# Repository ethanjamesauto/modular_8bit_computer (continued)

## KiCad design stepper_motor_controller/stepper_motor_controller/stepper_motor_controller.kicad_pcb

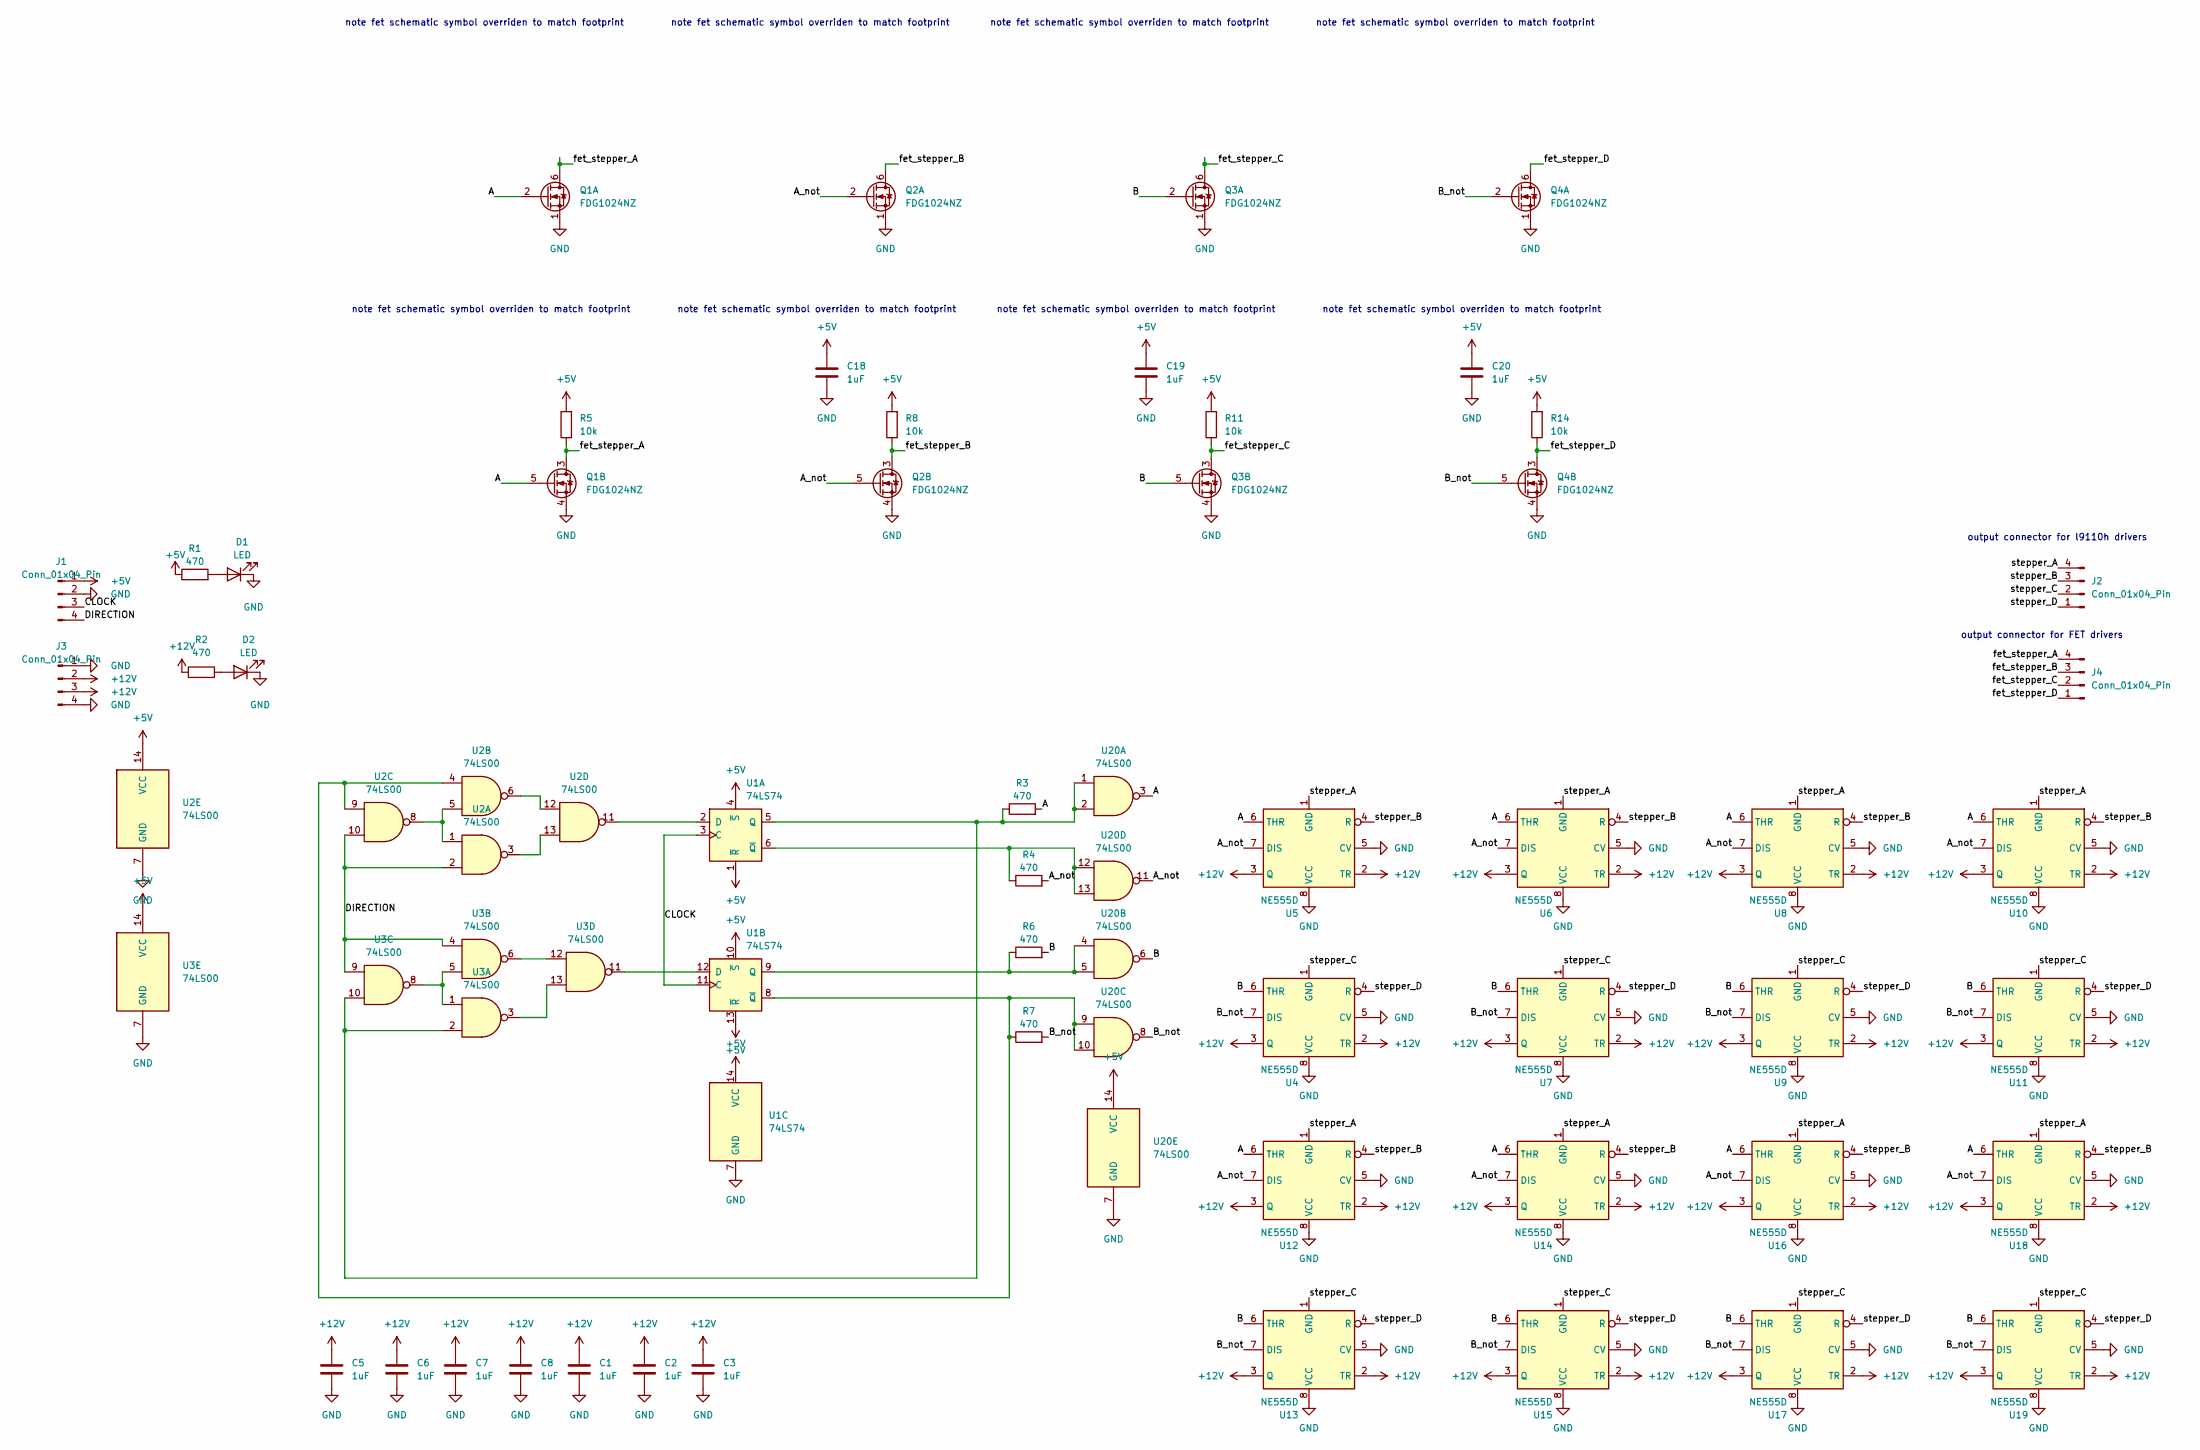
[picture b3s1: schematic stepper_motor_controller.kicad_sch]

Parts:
C1, C2, C3, C5, C6, C7, C8, C18, C19, C20: 1uF; C_0603_1608Metric
D1, D2: LED; R_0603_1608Metric
J1, J2, J3, J4: Conn_01x04_Pin; PinHeader_1x04_P2.54mm_Vertical
Q1, Q2, Q3, Q4: FDG1024NZ; SOT-23-6_Handsoldering
R1, R2, R3, R4, R6, R7: 470; R_0603_1608Metric
R5, R8, R11, R14: 10k; R_Axial_DIN0204_L3.6mm_D1.6mm_P5.08mm_Horizontal
U1: 74LS74; DIP-14_W7.62mm
U2, U3, U20: 74LS00; DIP-14_W7.62mm
U4, U5, U6, U7, U8, U9, U10, U11, U12, U13, U14, U15, U16, U17, U18, U19: NE555D; DIP-8_W7.62mm

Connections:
+5V: C18.1, C19.1, C20.1, J1.1, R1.1, R5.2, R8.2, R11.2, R14.2, U1.1 (~R), U1.4 (~S), U1.10 (~S), U1.13 (~R), U1.14 (VCC), U2.14 (VCC), U3.14 (VCC), U20.14 (VCC)
+12V: C1.1, C2.1, C3.1, C5.1, C6.1, C7.1, C8.1, J3.2, J3.3, R2.1, U4.2 (TR), U4.3 (Q), U5.2 (TR), U5.3 (Q), U6.2 (TR), U6.3 (Q), U7.2 (TR), U7.3 (Q), U8.2 (TR), U8.3 (Q), U9.2 (TR), U9.3 (Q), U10.2 (TR), U10.3 (Q), U11.2 (TR), U11.3 (Q), U12.2 (TR), U12.3 (Q), U13.2 (TR), U13.3 (Q), U14.2 (TR), U14.3 (Q), U15.2 (TR), U15.3 (Q), U16.2 (TR), U16.3 (Q), U17.2 (TR), U17.3 (Q), U18.2 (TR), U18.3 (Q), U19.2 (TR), U19.3 (Q)
/A: Q1.2 (G), Q1.5 (G), R3.2, U5.6 (THR), U6.6 (THR), U8.6 (THR), U10.6 (THR), U12.6 (THR), U14.6 (THR), U16.6 (THR), U18.6 (THR), U20.3
/A_not: Q2.2 (G), Q2.5 (G), R4.2, U5.7 (DIS), U6.7 (DIS), U8.7 (DIS), U10.7 (DIS), U12.7 (DIS), U14.7 (DIS), U16.7 (DIS), U18.7 (DIS), U20.11
/B: Q3.2 (G), Q3.5 (G), R6.2, U4.6 (THR), U7.6 (THR), U9.6 (THR), U11.6 (THR), U13.6 (THR), U15.6 (THR), U17.6 (THR), U19.6 (THR), U20.6
/B_not: Q4.2 (G), Q4.5 (G), R7.2, U4.7 (DIS), U7.7 (DIS), U9.7 (DIS), U11.7 (DIS), U13.7 (DIS), U15.7 (DIS), U17.7 (DIS), U19.7 (DIS), U20.8
/CLOCK: J1.3, U1.3 (C), U1.11 (C)
/DIRECTION: J1.4, U2.2, U2.10, U3.4, U3.9
/fet_stepper_A: J4.4, Q1.3 (D), Q1.6 (D), R5.1
/fet_stepper_B: J4.3, Q2.3 (D), Q2.6 (D), R8.1
/fet_stepper_C: J4.2, Q3.3 (D), Q3.6 (D), R11.1
/fet_stepper_D: J4.1, Q4.3 (D), Q4.6 (D), R14.1
/stepper_A: J2.4, U5.1 (GND), U6.1 (GND), U8.1 (GND), U10.1 (GND), U12.1 (GND), U14.1 (GND), U16.1 (GND), U18.1 (GND)
/stepper_B: J2.3, U5.4 (R), U6.4 (R), U8.4 (R), U10.4 (R), U12.4 (R), U14.4 (R), U16.4 (R), U18.4 (R)
/stepper_C: J2.2, U4.1 (GND), U7.1 (GND), U9.1 (GND), U11.1 (GND), U13.1 (GND), U15.1 (GND), U17.1 (GND), U19.1 (GND)
/stepper_D: J2.1, U4.4 (R), U7.4 (R), U9.4 (R), U11.4 (R), U13.4 (R), U15.4 (R), U17.4 (R), U19.4 (R)
GND: C1.2, C2.2, C3.2, C5.2, C6.2, C7.2, C8.2, C18.2, C19.2, C20.2, D1.1 (K), D2.1 (K), J1.2, J3.1, J3.4, Q1.1 (S), Q1.4 (S), Q2.1 (S), Q2.4 (S), Q3.1 (S), Q3.4 (S), Q4.1 (S), Q4.4 (S), U1.7 (GND), U2.7 (GND), U3.7 (GND), U4.5 (CV), U4.8 (VCC), U5.5 (CV), U5.8 (VCC), U6.5 (CV), U6.8 (VCC), U7.5 (CV), U7.8 (VCC), U8.5 (CV), U8.8 (VCC), U9.5 (CV), U9.8 (VCC), U10.5 (CV), U10.8 (VCC), U11.5 (CV), U11.8 (VCC), U12.5 (CV), U12.8 (VCC), U13.5 (CV), U13.8 (VCC), U14.5 (CV), U14.8 (VCC), U15.5 (CV), U15.8 (VCC), U16.5 (CV), U16.8 (VCC), U17.5 (CV), U17.8 (VCC), U18.5 (CV), U18.8 (VCC), U19.5 (CV), U19.8 (VCC), U20.7 (GND)
unnamed: D1.2 (A), R1.2
unnamed: D2.2 (A), R2.2
unnamed: U1.2 (D), U2.11
unnamed: R3.1, U1.5 (Q), U3.2, U3.10, U20.1, U20.2
unnamed: R4.1, U1.6 (~Q), U20.12, U20.13
unnamed: U1.12 (D), U3.11
unnamed: R6.1, U1.9 (Q), U20.4, U20.5
unnamed: R7.1, U1.8 (~Q), U2.4, U2.9, U20.9, U20.10
unnamed: U2.1, U2.5, U2.8
unnamed: U2.6, U2.12
unnamed: U2.3, U2.13
unnamed: U3.1, U3.5, U3.8
unnamed: U3.6, U3.12
unnamed: U3.3, U3.13

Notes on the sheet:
note fet schematic symbol overriden to match footprint
output connector for l9110h drivers
output connector for FET drivers

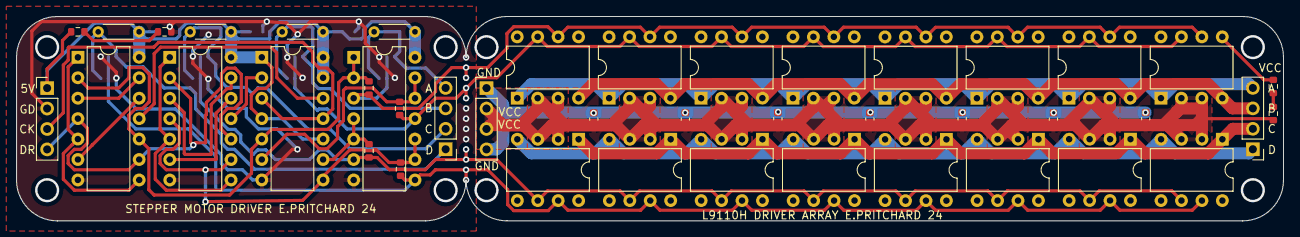
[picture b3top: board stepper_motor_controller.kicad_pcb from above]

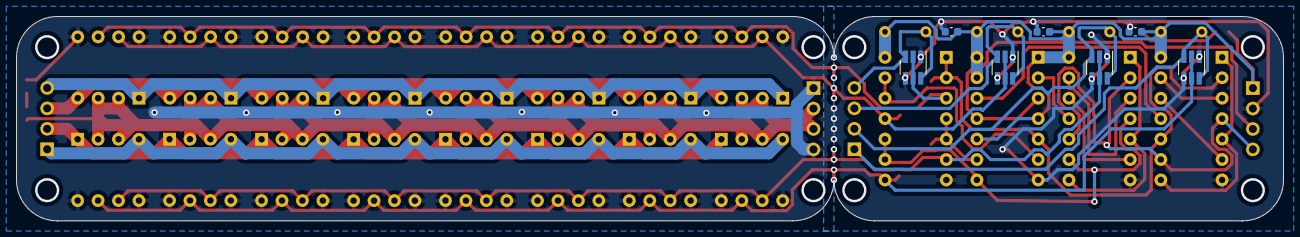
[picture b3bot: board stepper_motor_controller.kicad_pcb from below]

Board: 2 copper layers, 157.5 x 25.4 mm, 50 parts (7 on the bottom side), 31 nets.

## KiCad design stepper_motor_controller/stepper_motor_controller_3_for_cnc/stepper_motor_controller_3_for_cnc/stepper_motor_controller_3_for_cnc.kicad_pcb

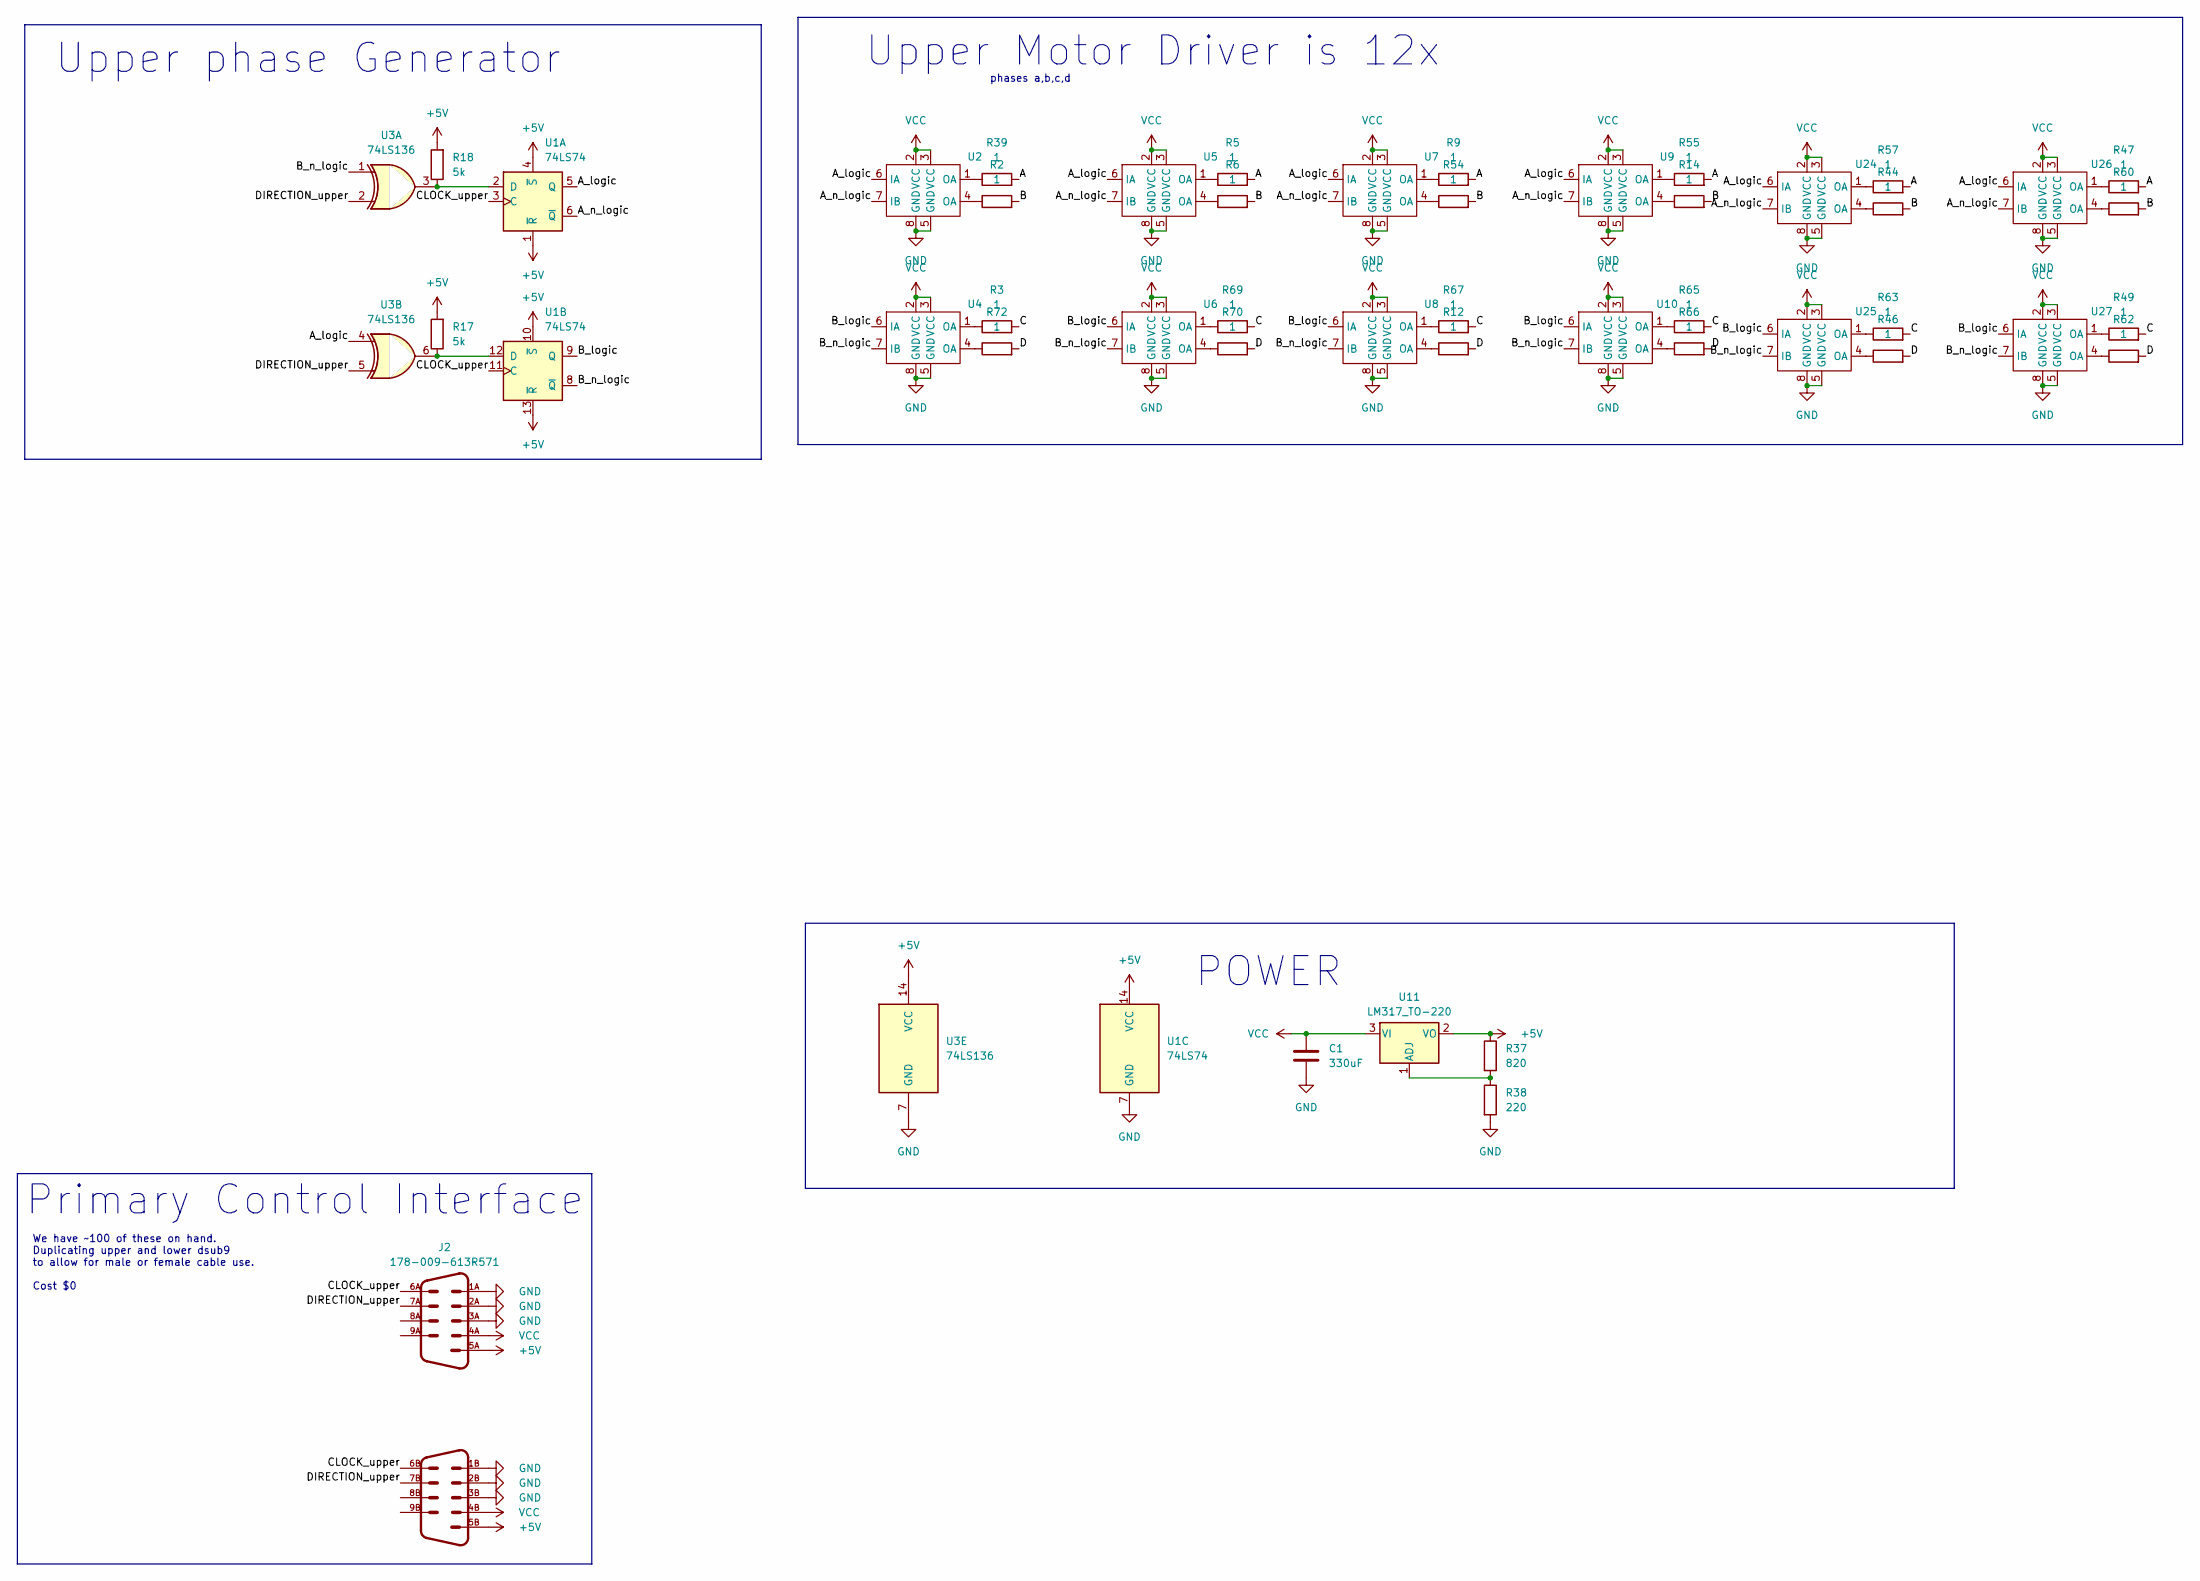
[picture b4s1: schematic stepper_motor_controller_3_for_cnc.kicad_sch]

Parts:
C1: 330uF
J2: 178-009-613R571
R2, R3, R5, R6, R9, R12, R14, R39, R44, R46, R47, R49, R54, R55, R57, R60, R62, R63, R65, R66, R67, R69, R70, R72: 1; R_1206_3216Metric
R17, R18: 5k; R_Axial_DIN0204_L3.6mm_D1.6mm_P5.08mm_Horizontal
R37: 820; R_Axial_DIN0204_L3.6mm_D1.6mm_P5.08mm_Horizontal
R38: 220; R_Axial_DIN0204_L3.6mm_D1.6mm_P5.08mm_Horizontal
U1: 74LS74; DIP-14_W7.62mm
U2, U4, U5, U6, U7, U8, U9, U10, U24, U25, U26, U27: DIP-8_W7.62mm
U3: 74LS136; DIP-14_W7.62mm
U11: LM317_TO-220; TO-220-3_Vertical

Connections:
+5V: J2.5A, J2.5B, R17.2, R18.2, R37.1, U1.1 (~R), U1.4 (~S), U1.10 (~S), U1.13 (~R), U1.14 (VCC), U3.14 (VCC), U11.2 (VO)
/A: R5.2, R9.2, R39.2, R47.2, R55.2, R57.2
/A_logic: U1.5 (Q), U2.6 (IA), U3.4, U5.6 (IA), U7.6 (IA), U9.6 (IA), U24.6 (IA), U26.6 (IA)
/A_n_logic: U1.6 (~Q), U2.7 (IB), U5.7 (IB), U7.7 (IB), U9.7 (IB), U24.7 (IB), U26.7 (IB)
/B: R2.2, R6.2, R14.2, R44.2, R54.2, R60.2
/B_logic: U1.9 (Q), U4.6 (IA), U6.6 (IA), U8.6 (IA), U10.6 (IA), U25.6 (IA), U27.6 (IA)
/B_n_logic: U1.8 (~Q), U3.1, U4.7 (IB), U6.7 (IB), U8.7 (IB), U10.7 (IB), U25.7 (IB), U27.7 (IB)
/C: R3.2, R49.2, R63.2, R65.2, R67.2, R69.2
/CLOCK_upper: J2.6A, J2.6B, U1.3 (C), U1.11 (C)
/D: R12.2, R46.2, R62.2, R66.2, R70.2, R72.2
/DIRECTION_upper: J2.7A, J2.7B, U3.2, U3.5
GND: C1.2, J2.1A, J2.1B, J2.2A, J2.2B, J2.3A, J2.3B, R38.2, U1.7 (GND), U2.5 (GND), U2.8 (GND), U3.7 (GND), U4.5 (GND), U4.8 (GND), U5.5 (GND), U5.8 (GND), U6.5 (GND), U6.8 (GND), U7.5 (GND), U7.8 (GND), U8.5 (GND), U8.8 (GND), U9.5 (GND), U9.8 (GND), U10.5 (GND), U10.8 (GND), U24.5 (GND), U24.8 (GND), U25.5 (GND), U25.8 (GND), U26.5 (GND), U26.8 (GND), U27.5 (GND), U27.8 (GND)
unnamed: R2.1, U2.4 (OA)
unnamed: R3.1, U4.1 (OA)
unnamed: R5.1, U5.1 (OA)
unnamed: R6.1, U5.4 (OA)
unnamed: R9.1, U7.1 (OA)
unnamed: R12.1, U8.4 (OA)
unnamed: R14.1, U9.4 (OA)
unnamed: R39.1, U2.1 (OA)
unnamed: R44.1, U24.4 (OA)
unnamed: R46.1, U25.4 (OA)
unnamed: R47.1, U26.1 (OA)
unnamed: R49.1, U27.1 (OA)
unnamed: R54.1, U7.4 (OA)
unnamed: R55.1, U9.1 (OA)
unnamed: R57.1, U24.1 (OA)
unnamed: R60.1, U26.4 (OA)
unnamed: R62.1, U27.4 (OA)
unnamed: R63.1, U25.1 (OA)
unnamed: R65.1, U10.1 (OA)
unnamed: R66.1, U10.4 (OA)
unnamed: R67.1, U8.1 (OA)
unnamed: R69.1, U6.1 (OA)
unnamed: R70.1, U6.4 (OA)
unnamed: R72.1, U4.4 (OA)
unnamed: R18.1, U1.2 (D), U3.3
unnamed: R17.1, U1.12 (D), U3.6
unnamed: R37.2, R38.1, U11.1 (ADJ)
VCC: C1.1, J2.4A, J2.4B, U2.2 (VCC), U2.3 (VCC), U4.2 (VCC), U4.3 (VCC), U5.2 (VCC), U5.3 (VCC), U6.2 (VCC), U6.3 (VCC), U7.2 (VCC), U7.3 (VCC), U8.2 (VCC), U8.3 (VCC), U9.2 (VCC), U9.3 (VCC), U10.2 (VCC), U10.3 (VCC), U11.3 (VI), U24.2 (VCC), U24.3 (VCC), U25.2 (VCC), U25.3 (VCC), U26.2 (VCC), U26.3 (VCC), U27.2 (VCC), U27.3 (VCC)

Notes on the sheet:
Primary Control Interface
We have ~100 of these on hand. Duplicating upper and lower dsub9 to allow for male or female cable use. Cost $0
phases a,b,c,d
Upper Motor Driver is 12x
POWER
Upper phase Generator

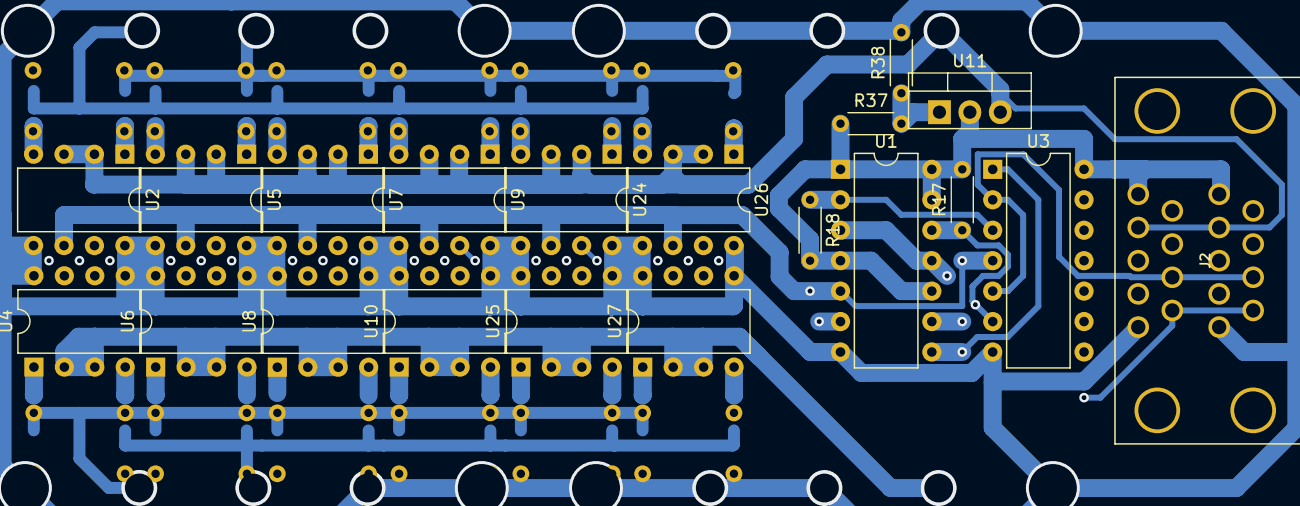
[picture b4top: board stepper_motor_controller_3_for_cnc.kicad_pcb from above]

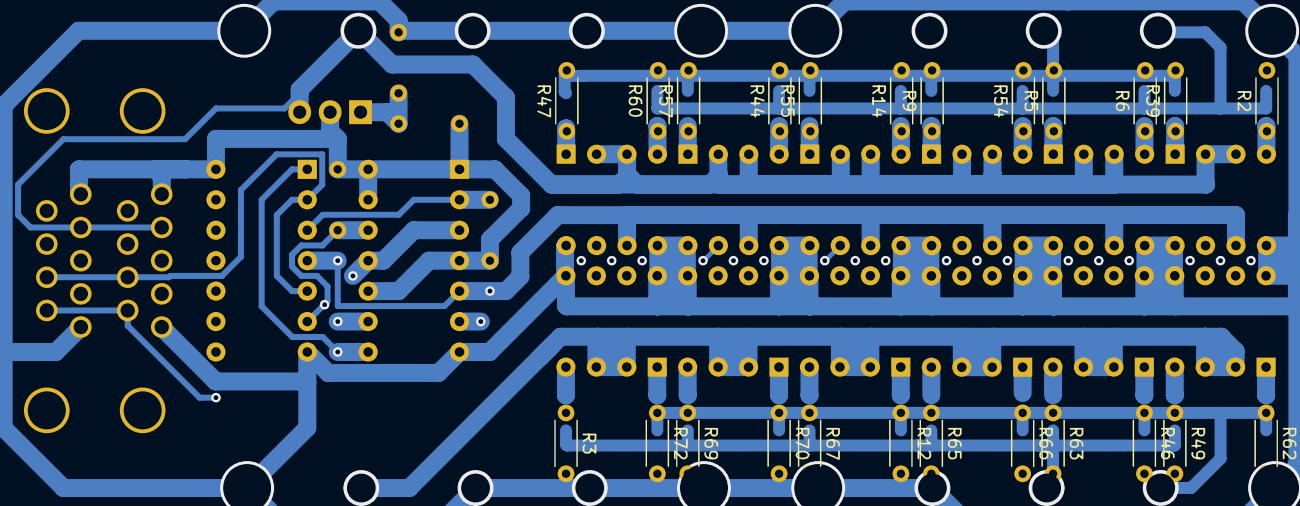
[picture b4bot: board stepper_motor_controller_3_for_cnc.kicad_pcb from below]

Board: 2 copper layers, 44 parts (24 on the bottom side), 40 nets.
